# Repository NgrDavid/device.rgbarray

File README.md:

## Harp RGB Array

Controls 2 arrays of colored LEDs according to RGB scale (Up to 32 LED on each array). Each LED has an associated index.

### Key Features ###

* Supports two LED array stripes
* Each stripe can have up to 32 LEDs
* Configurable color and intensity of each LED

### Connectivity ###

* 1x clock sync input (CLKIN) [stereo jack]
* 1x USB (for computer) [USB type C]
* 1x 12V supply [barrel connector jack]
* 1x I/O interface (5x general-purpose digital outputs DO0-DO4, 1x general purpose digital input DI0) [screw terminal]
* 1x digital output (DO0) [BNC]
* 1x digital input (DI0) [BNC]
* 1x Array 0 (G, S, 5V) [flick lock and screw terminal]
* 1x Array 1 (G, S, 5V) [flick lock and screw terminal]

## Interface ##

The interface with the Harp board can be done through [Bonsai](https://bonsai-rx.org/) or a dedicated GUI (Graphical User Interface).

In order to use this GUI, there are some software that needs to be installed:

1 - Install the [drivers](https://bitbucket.org/fchampalimaud/downloads/downloads/UsbDriver-2.12.26.zip).

2 - Install the [runtime](https://bitbucket.org/fchampalimaud/downloads/downloads/Runtime-1.0.zip).

3 - Reboot the computer.

4 - Install the [GUI](https://bitbucket.org/fchampalimaud/downloads/downloads/Harp%20RGB%20Array%20v1.0.0.zip).

## Licensing ##

Each subdirectory will contain a license or, possibly, a set of licenses if it involves both hardware and software.

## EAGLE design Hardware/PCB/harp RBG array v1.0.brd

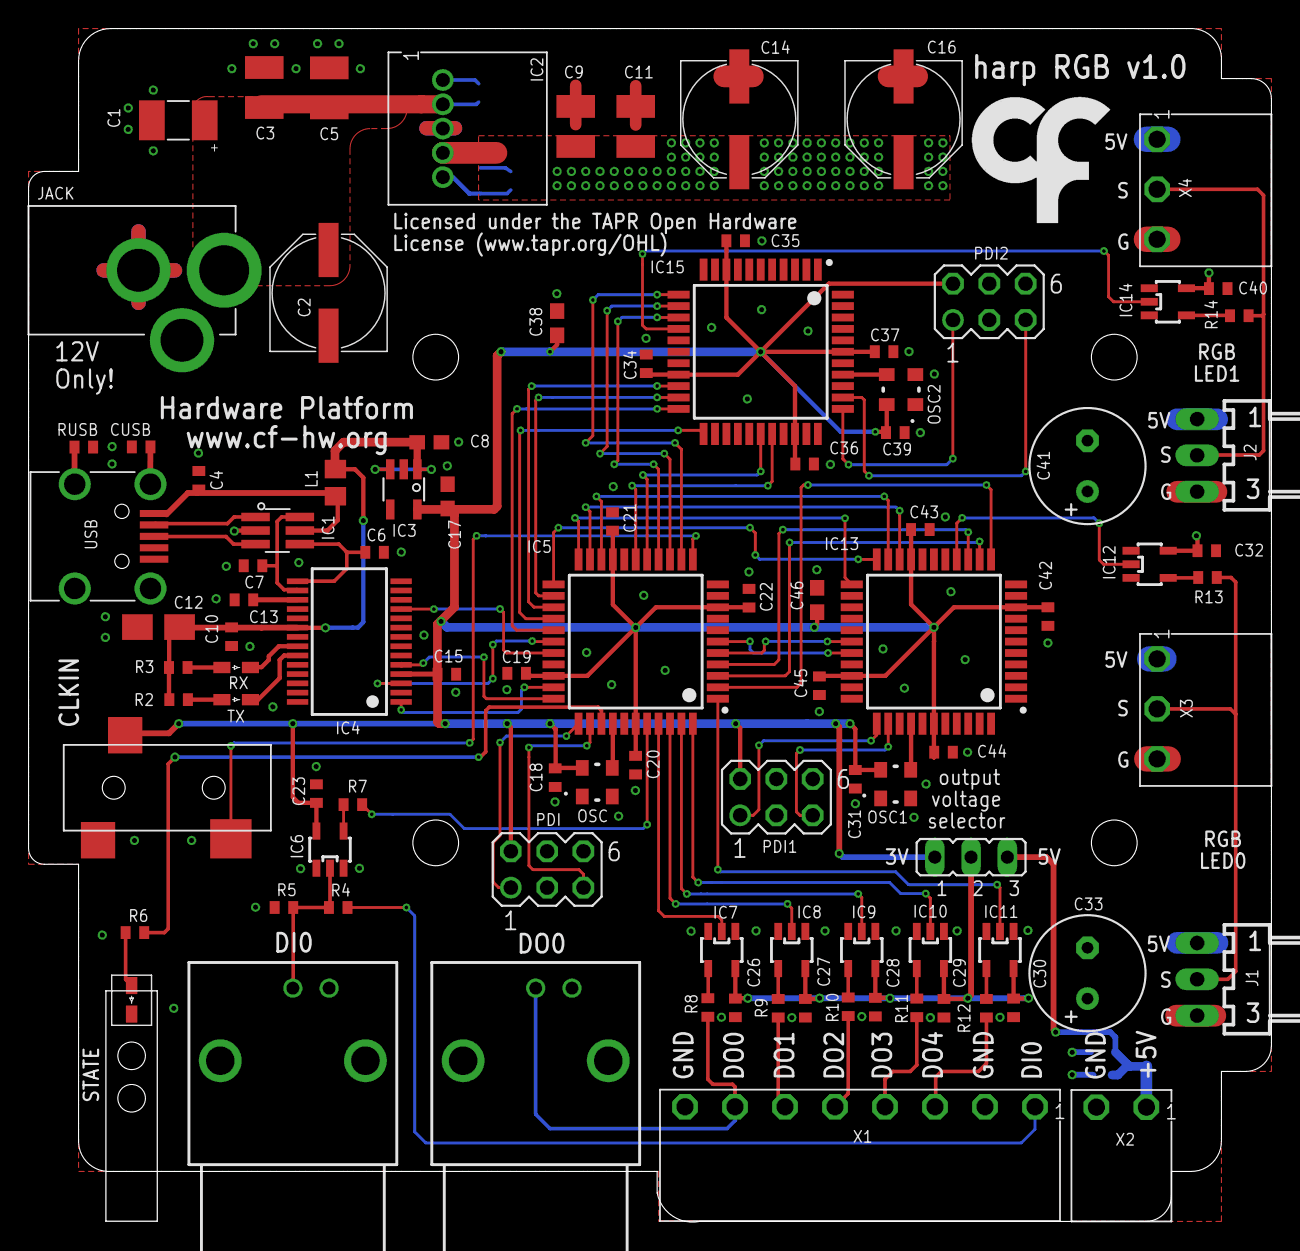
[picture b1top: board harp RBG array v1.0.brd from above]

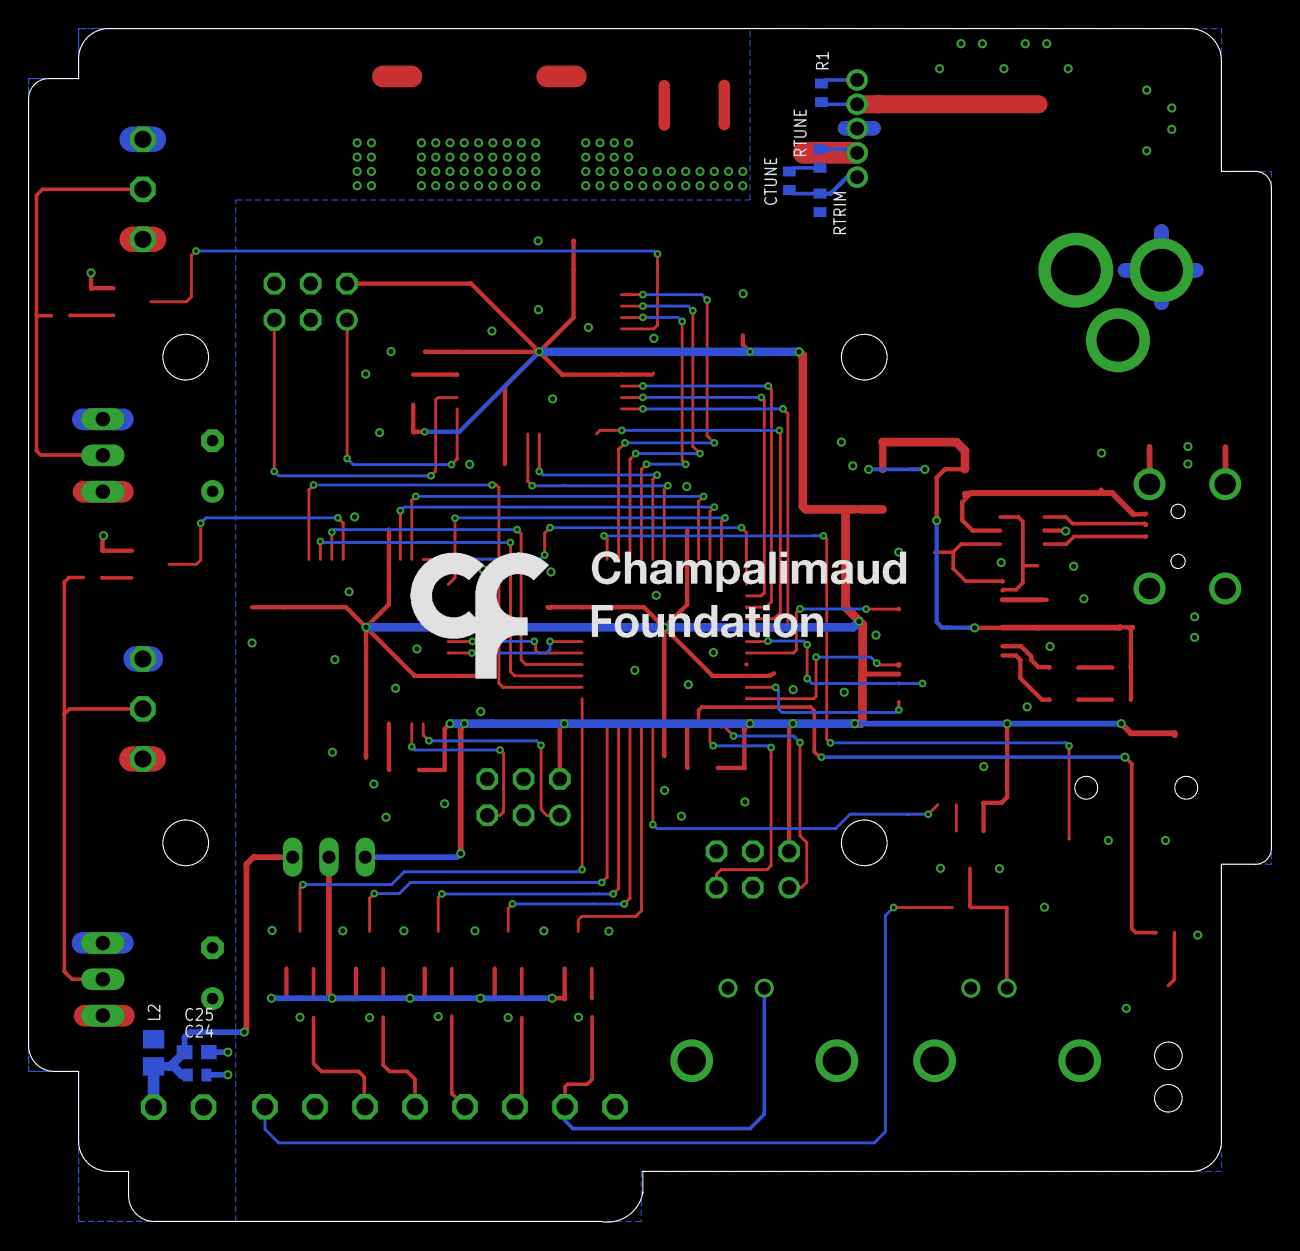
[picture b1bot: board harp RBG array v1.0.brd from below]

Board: 2 copper layers, 87.0 x 83.5 mm, 106 parts (8 on the bottom side), 81 nets.

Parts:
C1: 22uF; CAP_100UF_HAND
C2: 100uF; PANASONIC_E
C3, C5, C9: 22uF; C1210
C4, C10, C13, C15, C18, C19, C21, C22, C23, C24, C26, C27, C28, C29, C30, C31, C32, C34, C35, C37, C39, C40, C42, C43, C45: 100nF; C0402
C6, C7: 47pF; C0402
C8, C17, C25, C38, C46: 10uF; C0603
C11: NA; C1210
C12: 4.7uF; A/3216-18W
C14, C16: 270uF; PANASONIC_E
C20, C36, C44: 330nF; C0402
C33, C41: 470uF; E3,5-8
CLKIN: 35RASMT2BHNTRX
CTUNE: NA; C0402
CUSB: 4.7nF; C0402
IC1: USBLC6-2SC6; SOT23-6L
IC2: DC-DC-SIP-5; SIP-5
IC3: LP5907MFX-3.3; TSOT23-5
IC4: FT232RL; SSOP28
IC5, IC13, IC15: ATXMEGAxxxA4U-AU; QFP80P1200X1200X120-44N
IC6, IC7, IC8, IC9, IC10, IC11: SN74LVC1G125; SOT23-5
IC12, IC14: M74VHC1GT50DTT1G; SOT23-5
IN1: BNC; BNC_RA
J1, J2: 22-05-7038-03; 7395-03
JACK: DC_JACK2.1MM; DC_POWER_INPUT_2.1MM
JP1: JP2
L1: ???; R0805
L2: 600@100M; R0805
OSC, OSC1, OSC2: OSCILLATOR_3.2X2.5
OUT1: BNC; BNC_RA
PDI, PDI1, PDI2: MA03-2
R1: NA; R0402
R2: 2050 NA; R0402
R3: 680 NA; R0402
R4: 330; R0402
R5: 100k; R0402
R6: 68; R0402
R7, R8, R9, R10, R11, R12: 33; R0402
R13, R14: 100; R0402
RTRIM: 267; R0402
RTUNE: NA; R0402
RUSB: 1M; R0402
RX: GREEN NA; LED_HAND
STATE: GREEN; LED_HAND
TX: RED NA; LED_HAND
U$1: LED_PIPE_7513D2-L
U$3: LOGO_5
U$9: LOGO_6
USB: 240-0002-1
X1: CON_3.5MM_1X8
X2: CON_3.5MM_1X2
X3, X4: CON_3.5MM_1X3

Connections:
5V_RAW: C8.1, C10.1, C12.+, IC3.1, IC3.3, IC4.20, L1.1, R2.2, R3.2
+5V: C9.1, C11.1, C14.+, C16.+, C32.1, C33.+, C40.1, C41.+, IC2.P4, IC12.5, IC14.5, J1.1, J2.1, L2.1, RTUNE.2, X3.P1, X4.P1
+5V_F: C24.2, C25.2, JP1.3, L2.2, X2.P1
+12V: C1.+, C2.+, C3.1, C5.1, IC2.P2, JACK.P1, R1.2
+V: C26.1, C27.1, C28.1, C29.1, C30.1, IC7.5, IC8.5, IC9.5, IC10.5, IC11.5, JP1.2
AUX0_CTS: IC5.20, IC13.21
AUX0_RTS: IC5.21, IC13.20
AUX0_RXD: IC5.22, IC13.23
AUX0_TXD: IC5.23, IC13.22
AUX1_CTS: IC5.24, IC15.21
AUX1_RTS: IC5.25, IC15.20
AUX1_RXD: IC5.26, IC15.23
AUX1_TXD: IC5.27, IC15.22
BNC_DI0: IC6.2, IN1.1, R4.2, R5.2
CLK_SYNC: CLKIN.4, IC5.12
DEMO_MODE0: IC5.4, IC13.14
DEMO_MODE1: IC5.15, IC15.14
DI0: R4.1, X1.P1
DISABLE_LEDS0: IC5.3, IC13.13
DISABLE_LEDS1: IC5.14, IC15.13
DO0: OUT1.1, R8.2, X1.P7
DO1: R9.2, X1.P6
DO2: R10.2, X1.P5
DO3: R11.2, X1.P4
DO4: R12.2, X1.P3
DUMMY0_0: IC5.5, IC13.28
DUMMY0_1: IC5.16, IC15.28
DUMMY1_0: IC5.6, IC13.29
DUMMY1_1: IC5.17, IC15.29
FT_CTS: IC4.11, IC5.29
FT_RTS: IC4.3, IC5.28
FT_RXD: IC4.5, IC5.33
FT_TXD: IC4.1, IC5.32
GND: C1.-, C2.-, C3.2, C4.2, C5.2, C6.2, C7.2, C8.2, C9.2, C10.2, C11.2, C12.-, C13.2, C14.-, C15.2, C16.-, C17.2, C18.2, C19.2, C20.2, C21.2, C22.2, C23.2, C24.1, C25.1, C26.2, C27.2, C28.2, C29.2, C30.2, C31.2, C32.2, C33.-, C34.2, C35.2, C36.2, C37.2, C38.2, C39.2, C40.2, C41.-, C42.2, C43.2, C44.2, C45.2, C46.2, CLKIN.5, CUSB.2, IC1.P$2, IC2.P3, IC3.2, IC4.7, IC4.18, IC4.21, IC4.25, IC4.26, IC5.8, IC5.18, IC5.30, IC5.38, IC6.1, IC6.3, IC7.1, IC7.3, IC8.1, IC8.3, IC9.1, IC9.3, IC10.1, IC10.3, IC11.1, IC11.3, IC12.1, IC12.3, IC13.8, IC13.18, IC13.30, IC13.38, IC14.1, IC14.3, IC15.8, IC15.18, IC15.30, IC15.38, IN1.2, J1.3, J2.3, JACK.P2, JACK.P3, OSC.P$2, OSC1.P$2, OSC2.P$2, OUT1.2, PDI.6, PDI1.6, PDI2.6, R5.1, RTRIM.1, RUSB.2, STATE.K, USB.P$5, X1.P2, X1.P8, X2.P2, X3.P3, X4.P3
IN0: IC5.40, R7.2
LED_DATA0: IC12.2, IC13.15
LED_DATA1: IC14.2, IC15.15
unnamed: IC14.4, R14.2
unnamed: IC6.4, R7.1
unnamed: IC8.4, R9.1
unnamed: IC7.4, R8.1
unnamed: IC9.4, R10.1
unnamed: IC10.4, R11.1
unnamed: IC11.4, R12.1
unnamed: CTUNE.2, IC2.P5, RTRIM.2
unnamed: IC12.4, R13.2
unnamed: CTUNE.1, RTUNE.1
unnamed: IC2.P1, R1.1
unnamed: R6.1, STATE.A
unnamed: C13.1, IC4.17
unnamed: C4.1, IC1.P$5, L1.2, USB.P$1
unnamed: IC1.P$1, USB.P$2
unnamed: R3.1, RX.A
unnamed: IC4.23, TX.K
unnamed: IC4.22, RX.K
unnamed: IC1.P$3, USB.P$3
unnamed: CUSB.1, USB.SHIELD_4
unnamed: RUSB.1, USB.SHIELD_1
unnamed: R2.1, TX.A
OSC1: IC13.37, OSC1.P$3
OSC2: IC5.37, OSC.P$3
OSC3: IC15.37, OSC2.P$3
OUT0: IC5.41, IC7.2
OUT1: IC5.42, IC8.2
OUT2: IC5.43, IC9.2
OUT3: IC5.44, IC10.2
OUT4: IC5.1, IC11.2
PDI-CLK: IC5.35, PDI.5
PDI-CLK0: IC13.35, PDI1.5
PDI-CLK1: IC15.35, PDI2.5
PDI-DATA: IC5.34, PDI.1
PDI-DATA0: IC13.34, PDI1.1
PDI-DATA1: IC15.34, PDI2.1
SERIAL_LED0: J1.2, R13.1, X3.P2
SERIAL_LED1: J2.2, R14.1, X4.P2
STATE: IC5.36, R6.2
UPDATE_LEDS0: IC5.2, IC13.12
UPDATE_LEDS1: IC5.13, IC15.12
USBDM: C7.1, IC1.P$6, IC4.16
USBDP: C6.1, IC1.P$4, IC4.15
VCCIO: C15.1, C17.1, C18.1, C19.1, C20.1, C21.1, C22.1, C23.1, C31.1, C34.1, C35.1, C36.1, C37.1, C38.1, C39.1, C42.1, C43.1, C44.1, C45.1, C46.1, CLKIN.1, IC3.5, IC4.4, IC5.9, IC5.19, IC5.31, IC5.39, IC6.5, IC13.9, IC13.19, IC13.31, IC13.39, IC15.9, IC15.19, IC15.31, IC15.39, JP1.1, OSC.P$4, OSC1.P$4, OSC2.P$4, PDI.2, PDI1.2, PDI2.2

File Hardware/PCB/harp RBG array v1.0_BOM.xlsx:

| Part(s) | Quantity | Description | Distributor | Part. No.
 | IC1 | 1 | ESD Protection Low Cap | Mouser | 511-USBLC6-2SC6Y
 | IC2 | 1 | Conversores CC/CC sem isolação 6-A 4.5V-14V Input Non-Iso Adj Pwr Mod | Mouser | 595-PTR08060WVD
 | IC3 | 1 | LDO 250mA Ultra-Lo Noise LDO Reg | Mouser | 595-LP5907MFX-3.3NPB
 | IC4 | 1 | IC USB USB to Serial UART Enhanced IC SSOP-28 | Mouser | 895-FT232RL
 | IC5 | 1 | Microcontroladores de 8 bits - MCU 44TQFP, IND TEMP GREEN, 1.6-3.6V | Mouser | 556-ATXMEGA128A4U-AU
 | IC13, IC15 | 2 | Microcontroladores de 8 bits - MCU AVR8 32KB FLSH 4KB | Mouser | 556-ATXMEGA32A4U-AU
 | IC6, IC7, IC8, IC9, IC10, IC11, IC12, IC14 | 8 | Buffers e line drivers 1.65-5.5V Single Non-Inverting TTL | Mouser | 863-M74VHC1GT50DTT1G
 | C6, C7 | 2 | CAP CER 47pF 50V ±5% C0G 0402 | Mouser | 77-VJ0402A470JXACBC
 | CUSB | 1 | CAP CER 4.7nF 100V ±10% X7R 0402 | Mouser | 81-GRM155R72A472KA01
 | C4, C10, C13, C15, C18, C19, C21, C22, C23, C24, C26, C27, C28, C29, C30, C31, 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 | 25 | CAP CER 100nF 10V X5R 0402 | REEL | REEL
 | C20, C36, C44 | 3 | CAP CER 0.33uF 10V ±10% X5R 0402 | Mouser | GRM155R61A334KE15D
 | C12 | 1 | CAP TAN 4.7uF 6.3V ±10% 1206 | Mouser | 80-T491A475K006
 | C8, C17, C25, C38, C46 | 5 | CAP CER 10uF 10V ±10% X5R 0603 | Mouser | 81-GRM188R61A106KE9D
 | C1 | 1 | CAP TAN 22uF 20V ±10% 1210 | Mouser | 667-20TQC22MYFB
 | C9 | 1 | CAP CER 22uF 16V ±10% X5R 1210 | Mouser | 81-GRM32ER61C226KE20
 | C3, C5 | 2 | CAP CER 22uF 25V ±10% X5R 1210 | Mouser | 81-GRM32ER61E226KE15
 | C2 | 1 | CAP ELE 100uF 25V ±20% | Mouser | 667-25SVF100M
 | C14, C16 | 2 | CAP ELE 270uF 16V ±20% | Mouser | 667-16SVF270M
 | C33, C41 | 2 | CAP ELE TH 470uF 16V 20% | Mouser | 667-EEU-FM1C471
 | R7, R8, R9, R10, R11, R12 | 6 | RES SMD 33Ω 5% 0402 | Mouser | 667-ERJ-2GEJ330X
 | R6 | 1 | RES SMD 68Ω 5% 0402 | Mouser | 71-CRCW0402-68-E3
 | R13, R14 | 2 | RES SMD 100Ω 1% 0402 | Mouser | 667-ERJ-2RKF1000X
 | RTRIM | 1 | RES SMD 267Ω 1% 0402 | Mouser | 667-ERJ-2RKF2670X
 | R4 | 1 | RES SMD 330Ω 1% 0402 | Mouser | 667-ERJ-PA2F3300X
 | R5 | 1 | RES SMD 100kΩ 1% 0402 | REEL | REEL
 | RUSB | 1 | RES SMD 1MΩ 1% 0402 | Mouser | 652-CR0402FX-1004GLF
 | STATE | 1 | LED, Green, 1.6mm x 0.8mm, 566 nm, 2.1 V, 20 mA, 15 mcd | Mouser | 78-TLMP1100-GS08
 | OSC, OSC1, OSC2 | 3 | 32MHz 10ppm | Mouser | 998-1001CI5032.0000T
 | CLKIN | 1 | SMT 3.5 STEREO REEL | Mouser | 502-35RASMT2BHNTRX
 | L1 | 1 | 40ohms 100MHz 1.5A Monolithic 0805 SMD | Mouser | 875-MI0805K400R-10
 | L2 | 1 | FERRITE BEAD 600Ω 500mA 300mΩ 0805 | Mouser | 875-HZ0805E601R-10
 | PDI, PDI1, PDI2 | 3 | 6P DR UNSHRD HRD | Mouser | 649-67996-206HLF
 | USB | 1 | UX60-MB-5S8 | Mouser | 798-UX60-MB-5S8
 | USB Cable | 1 | USB A - MINI-B 1M BLACK | Mouser | 538-88732-8602
 |  | 1 | Tubos de Luz LED CML LIGHTPIPE | Mouser | 606-7513D2-L
 | JACK | 1 | CC PCB 2.1MM | Mouser | 163-179PH-EX
 | IN1, OUT1 | 2 | Connectores RF / Connectores Coaxiais R.A. JACK 50 OHM | Mouser | 571-5227161-1
 | JP1 | 1 | 3POS Gold Male | Mouser | 649-68001-203HLF
 |  | 1 | SHUNT JUMPER, 2POS | Farnell | 2396301
 | WALL ADAPTER | 1 | AC/DC Power Supply, Level VI, Wall Mount, 1 Output, 24 W, 12 V, 2 A | Farnell | 2643258
 | J1, J2 | 2 | Right Angle, 2.54 mm, 3 Contacts, Header, KK 7395 Series, Through Hole | Farnell | 1360143
 | X2 | 1 | 20.1550M/2-E - Pluggable Terminal Block, 3.5 mm, 2 Ways, 28 AWG, 16 AWG, 1.5 mm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 | Farnell | 2575215
 | X3, X4 | 2 | 20.1550M/3-E - Pluggable Terminal Block, 3.5 mm, 3 Ways, 28 AWG, 16 AWG, 1.5 mm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 | Farnell | 2575216
 | X1 | 1 | 20.1550M/8-E - Pluggable Terminal Block, 3.5 mm, 8 Ways, 28 AWG, 16 AWG, 1.5 mm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 | Farnell | 2575220
 |  | 1 | 20.155MH/3-E - Terminal Block, Horizontal, Header, 3.5 mm, 3 Ways, 10 A | Farnell | 2517859
 |  | 2 | 20.155MH/2-E - Terminal Block, Horizontal, Header, 3.5 mm, 2 Ways, 10 A | Farnell | 2517858
 |  | 1 | 20.155MH/8-E - Terminal Block, Horizontal, Header, 3.5 mm, 8 Ways, 10 A | Farnell | 2517863
 |  | 8 | 1110030 - Nut, Hex, M3, Nylon 6.6, Pack of 50 | Farnell | 1110030
 |  | 4 | Machine Screw, M3, 10 mm, Nylon (Polyamide), Pan Head Slotted, PK25 | Farnell | 1514410
 | Components | 115
 | Licensed under the TAPR Open Hardware License (www.tapr.org/OHL)
 | Copyright 2017 Artur Silva and Filipe Carvalho

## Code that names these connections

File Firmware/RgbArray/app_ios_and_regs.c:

#include <avr/io.h>
#include "hwbp_core_types.h"
#include "app_ios_and_regs.h"

/************************************************************************/
/* Configure and initialize IOs                                         */
/************************************************************************/
void init_ios(void)
{	/* Configure input pins */
	io_pin2in(&PORTA, 0, PULL_IO_UP, SENSE_IO_EDGES_BOTH);               // DI0
	io_pin2in(&PORTB, 1, PULL_IO_DOWN, SENSE_IO_EDGES_BOTH);             // DUMMY0_0
	io_pin2in(&PORTB, 2, PULL_IO_DOWN, SENSE_IO_EDGES_BOTH);             // DUMMY1_0
	io_pin2in(&PORTC, 6, PULL_IO_DOWN, SENSE_IO_EDGES_BOTH);             // DUMMY0_1
	io_pin2in(&PORTC, 7, PULL_IO_DOWN, SENSE_IO_EDGES_BOTH);             // DUMMY1_1

	/* Configure input interrupts */
	io_set_int(&PORTA, INT_LEVEL_LOW, 0, (1<<0), false);                 // DI0

	/* Configure output pins */
	io_pin2out(&PORTA, 1, OUT_IO_DIGITAL, IN_EN_IO_EN);                  // DO0
	io_pin2out(&PORTA, 2, OUT_IO_DIGITAL, IN_EN_IO_EN);                  // DO1
	io_pin2out(&PORTA, 3, OUT_IO_DIGITAL, IN_EN_IO_EN);                  // DO2
	io_pin2out(&PORTA, 4, OUT_IO_DIGITAL, IN_EN_IO_EN);                  // DO3
	io_pin2out(&PORTA, 5, OUT_IO_DIGITAL, IN_EN_IO_EN);                  // DO4
	io_pin2out(&PORTA, 6, OUT_IO_DIGITAL, IN_EN_IO_EN);                  // UPDATE_LEDS0
	io_pin2out(&PORTA, 7, OUT_IO_DIGITAL, IN_EN_IO_EN);                  // DISABLE_LEDS0
	io_pin2out(&PORTC, 3, OUT_IO_DIGITAL, IN_EN_IO_EN);                  // UPDATE_LEDS1
	io_pin2out(&PORTC, 4, OUT_IO_DIGITAL, IN_EN_IO_EN);                  // DISABLE_LEDS1
	io_pin2out(&PORTB, 0, OUT_IO_DIGITAL, IN_EN_IO_EN);                  // DEMO_MODE0
	io_pin2out(&PORTC, 5, OUT_IO_DIGITAL, IN_EN_IO_EN);                  // DEMO_MODE1
	io_pin2out(&PORTB, 0, OUT_IO_DIGITAL, IN_EN_IO_EN);                  // DEMO_MODE0
	io_pin2out(&PORTC, 5, OUT_IO_DIGITAL, IN_EN_IO_EN);                  // DEMO_MODE1

	/* Initialize output pins */
	clr_DO0;
	clr_DO1;
	clr_DO2;
	clr_DO3;
	clr_DO4;
	clr_UPDATE_LEDS0;
	clr_DISABLE_LEDS0;
	clr_UPDATE_LEDS1;
	clr_DISABLE_LEDS1;
	clr_DEMO_MODE0;
	clr_DEMO_MODE1;
	clr_DEMO_MODE0;
	clr_DEMO_MODE1;
}

/************************************************************************/
/* Registers' stuff                                                     */
/************************************************************************/
AppRegs app_regs;

uint8_t app_regs_type[] = {
	TYPE_U8,
	TYPE_U8,
	TYPE_U8,
	TYPE_U8,
	TYPE_U8,
	TYPE_U8,
	TYPE_U8,
	TYPE_U8,
	TYPE_U8,
	TYPE_U8,
	TYPE_U8,
	TYPE_U8,
	TYPE_U8,
	TYPE_U8,
	TYPE_U8,
	TYPE_U8,
	TYPE_U8,
	TYPE_U16,
	TYPE_U8,
	TYPE_U8
};

uint16_t app_regs_n_elements[] = {
	1,
	1,
	192,
	96,
	96,
	3,
	1,
	1,
	1,
	1,
	1,
	1,
	1,
	1,
	1,
	1,
	1,
	1,
	1,
	1
};

uint8_t *app_regs_pointer[] = {
	(uint8_t*)(&app_regs.REG_LEDS_STATUS),
	(uint8_t*)(&app_regs.REG_LEDS_ON_BUS),
	(uint8_t*)(app_regs.REG_COLOR_ARRAY),
	(uint8_t*)(app_regs.REG_COLOR_ARRAY_BUS0),
	(uint8_t*)(app_regs.REG_COLOR_ARRAY_BUS1),
	(uint8_t*)(app_regs.REG_COLOR_OFF),
	(uint8_t*)(&app_regs.REG_RESERVED1),
	(uint8_t*)(&app_regs.REG_DI0_CONF),
	(uint8_t*)(&app_regs.REG_DO0_CONF),
	(uint8_t*)(&app_regs.REG_DO1_CONF),
	(uint8_t*)(&app_regs.REG_RESERVED2),
	(uint8_t*)(&app_regs.REG_LATCH_NEXT_UPDATE),
	(uint8_t*)(&app_regs.REG_INPUTS_STATE),
	(uint8_t*)(&app_regs.REG_OUTPUTS_SET),
	(uint8_t*)(&app_regs.REG_OUTPUTS_CLEAR),
	(uint8_t*)(&app_regs.REG_OUTPUTS_TOGGLE),
	(uint8_t*)(&app_regs.REG_OUTPUTS_OUT),
	(uint8_t*)(&app_regs.REG_PULSE_PERIOD),
	(uint8_t*)(&app_regs.REG_PULSE_COUNT),
	(uint8_t*)(&app_regs.REG_EVNT_ENABLE)
};

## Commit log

2018-05-16 Added .gitignore.
2018-05-16 Added the slaves' firmware VisualStudio Project.
2018-05-16 Corrected finish criteria of the demonstration.
2018-05-24 Added a new function to drive the RGBs. Ability to define dynamically the number of the RGBs on the bus.
2018-05-24 Increased RX buffer size.
2018-05-24 Added several functionalities.
2018-05-24 Added the first files of the master microcontroller.
2018-05-24 Removed the checksum from the protocol between master and slaves.
2018-05-24 Increased reliability on the LEDS_READY interrupts.
2018-05-24 Created an exclusive buffer for the demo mode.
2018-05-24 Change status events to UART instead of digital pins. Renamed pins to DUMMY. Renamed register bits. Added the rest of the functionalities (except the digital outputs handling).
2018-05-24 Corrected a small bug.
2018-05-24 Changed register LEDS_ON_BUS definition: it contains the number of LEDs on each bus.
2018-05-25 Implemented the digital outputs handling.
2018-05-25 Implemented the digital inputs and outputs configurations.
2018-05-25 Corrected digital outputs handling.
2018-05-25 Added code to the catastrophic_error_detected callback.
2018-05-25 Added digital outputs handling when the array is loaded into the driver.
2018-06-03 Renamed firmware folder Rgb to RgbArray.
2018-06-03 Added include to remove warnings.
2018-06-27 Replaced reserved register with registers for the pulse feature.
2018-06-27 Added register for the new functionality: latch array without update the RGB array.
2018-06-27 Implemented the pulse feature.
2018-06-27 Implemented the latch feature.
2018-06-27 Increased firmware version to 1.1.
2019-01-25 Added new register COLOR_OFF and the hability to configure the values when in standaby state.
2022-12-17 Add PCB and BOM files
2022-12-17 Add licenses and readme
2022-12-18 Correct typo
2022-12-18 refactor assets' folder structure
2022-12-23 refactor repository structure
2023-08-18 Add Generators
2023-08-18 Remove extensions
2023-08-18 First draft of schema and corresponding generated interface
2023-08-19 Clean up notes
2023-08-22 Update .gitignore file
2023-08-22 Update start core parameters
2023-08-23 Update PCB asset image
2023-08-23 Add .gitignore to Hardware
2023-08-23 Add Mechanical folder and license
2023-08-23 Update Mechanical License file
2023-08-23 Update .cppproj library path
2023-10-18 Minor naming changes
2024-07-24 Update interface csproj
2024-10-31 Update links on the README
2024-11-10 Update generators and regenerate interface
2024-11-10 Update package metadata and add library package
2024-11-10 Update device schema source
2025-05-16 Create basic CI/CD for interface package

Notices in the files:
Hardware/PCB/harp RBG array v1.0.brd:
Copyright 2018 Artur Silva and Filipe Carvalho
